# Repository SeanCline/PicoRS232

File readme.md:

# PicoRS232

>⚠ I haven't had this PCB design manufactured yet so there may be bugs. Here be dragons.

This PCB connects 6 RS232 UART ports to a Raspberry Pi Pico.
 1) Two ports are connected to the RP2040's 2 hardware UARTs.
 2) Four more ports are connected to the RP2040's PIO drivers for software UART.

The TX/RX pins line up with those from the [Pico UART Bridge](https://github.com/harrywalsh/pico-hw_and_pio-uart-gridge/tree/HW_and_pio_uarts) firmware so that firmware should work out-of-the-box.

Note: Flow control is not supported in this design. Only TX/RX are connected to each port. This was done to keep the BOM low and software simple.

## Schematic

## Board

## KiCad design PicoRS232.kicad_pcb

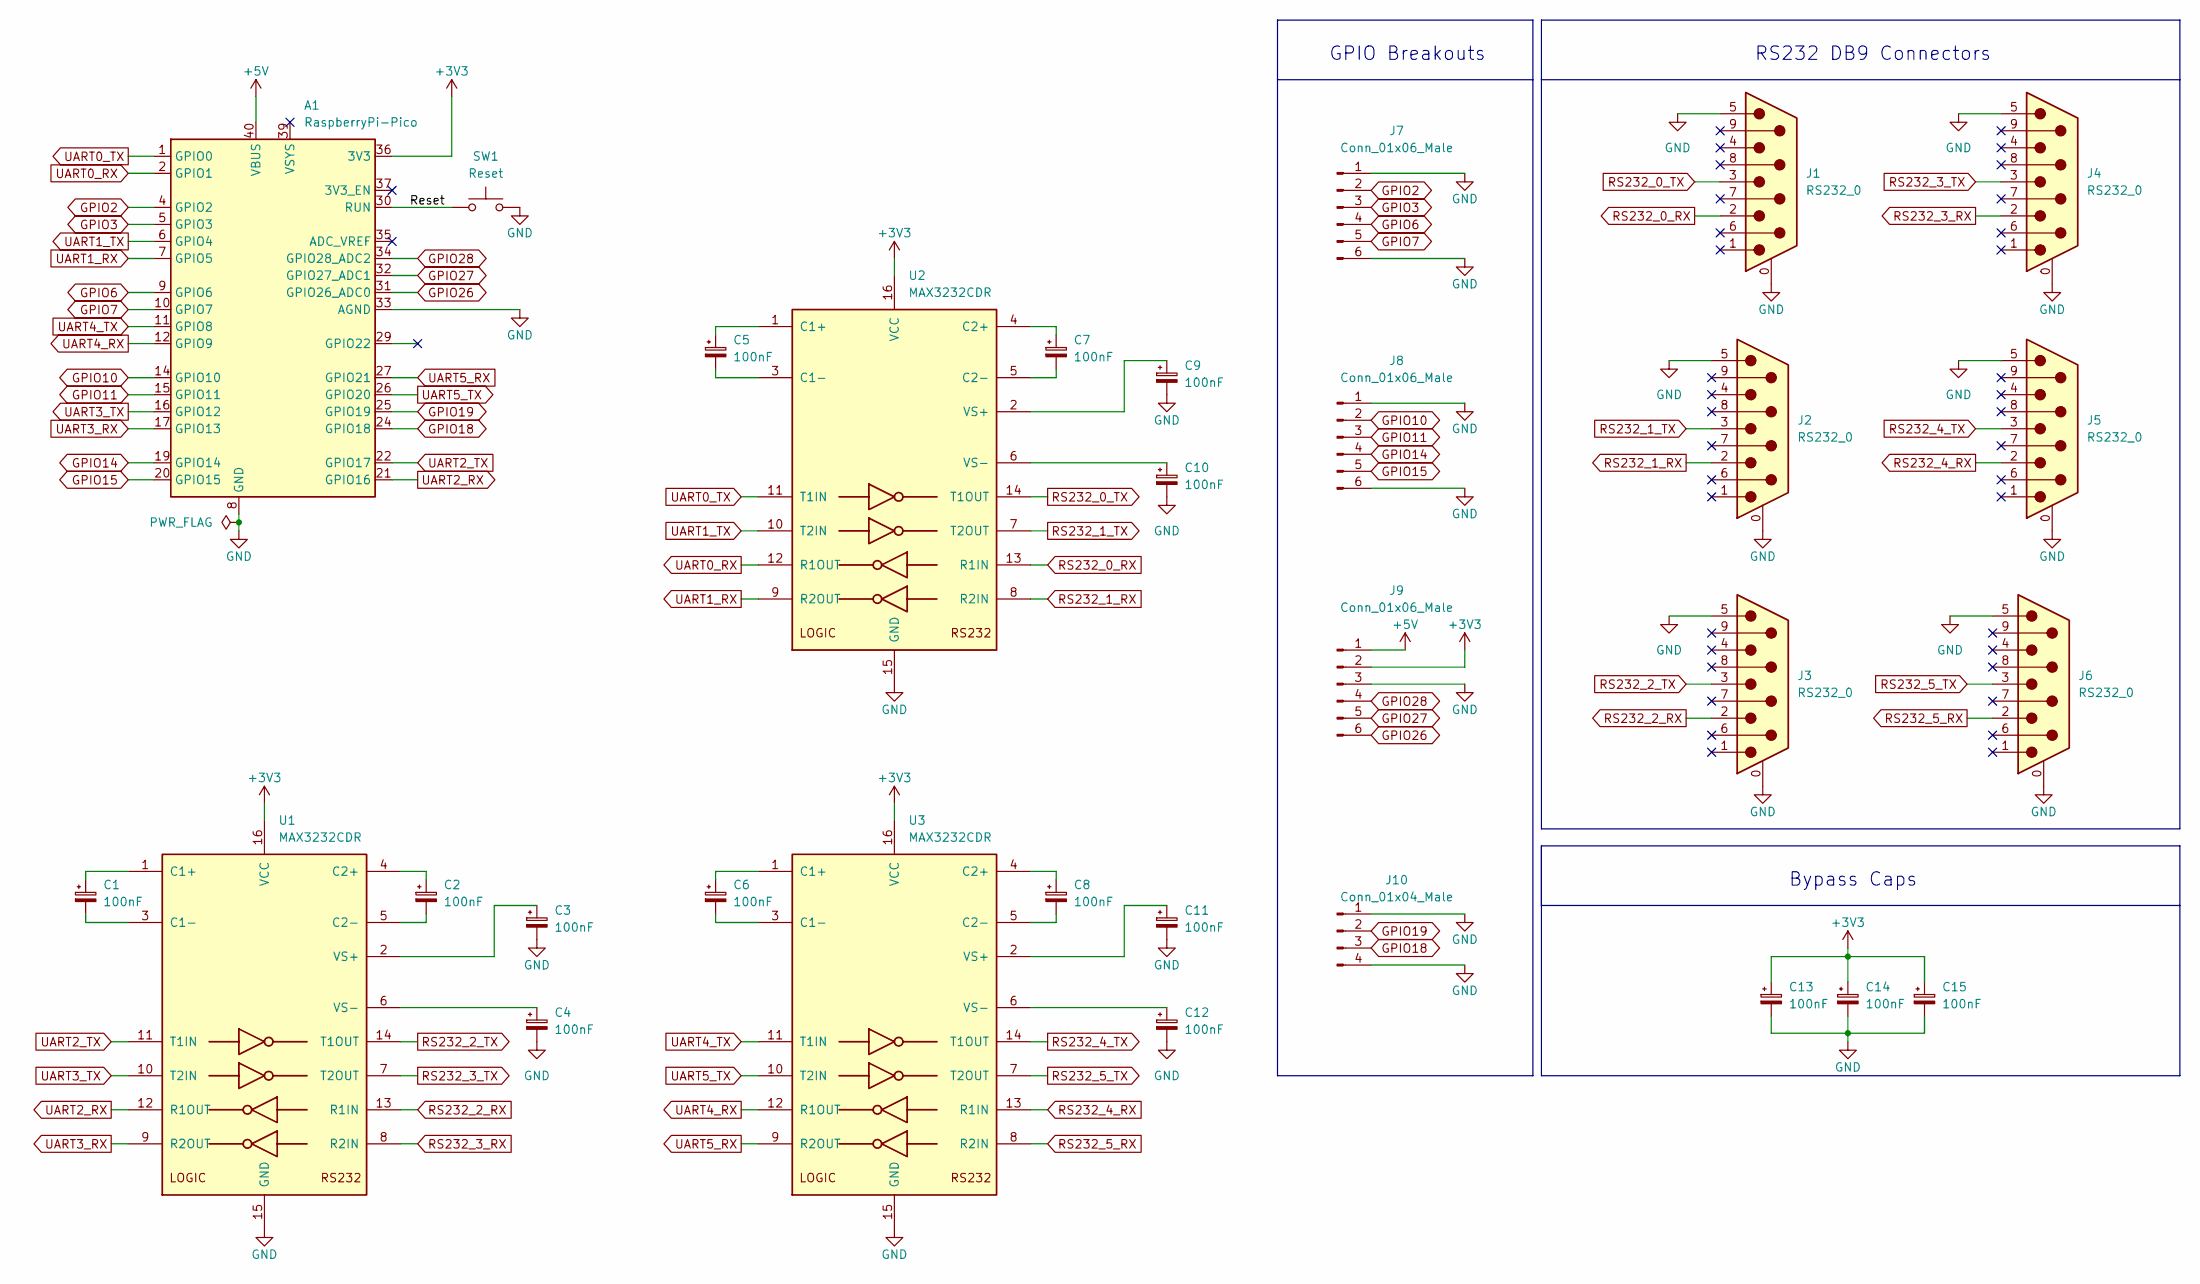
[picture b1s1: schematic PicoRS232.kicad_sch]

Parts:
A1: RaspberryPi-Pico; Raspberry_Pi_Pico_SMT_THT
C1, C2, C3, C4, C5, C6, C7, C8, C9, C10, C11, C12, C13, C14, C15: 100nF; C_0402_1005Metric; LCSC C307331
J1, J2, J3, J4, J5, J6: RS232_0; DSUB-9_Male_Horizontal_P2.77x2.84mm_EdgePinOffset7.70mm_Hou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; LCSC C141880
J7, J8, J9: Conn_01x06_Male; PinHeader_1x06_P2.54mm_Vertical; LCSC C225481
J10: Conn_01x04_Male; PinHeader_1x04_P2.54mm_Vertical; LCSC C225479
SW1: Reset; SW_SPST_SKQG_WithStem; LCSC C318889
U1, U2, U3: MAX3232CDR; SOIC-16_3.9x9.9mm_P1.27mm; LCSC C45843

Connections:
+3V3: A1.36 (3V3), C13.1, C14.1, C15.1, J9.2, U1.16 (VCC), U2.16 (VCC), U3.16 (VCC)
+5V: A1.40 (VBUS), J9.1
/Reset: A1.30 (RUN), SW1.1
GND: A1.3 (GND), A1.8 (GND), A1.13 (GND), A1.18 (GND), A1.23 (GND), A1.28 (GND), A1.33 (AGND), A1.38 (GND), C3.2, C4.2, C9.2, C10.2, C11.2, C12.2, C13.2, C14.2, C15.2, J1.0 (PAD), J1.5, J2.0 (PAD), J2.5, J3.0 (PAD), J3.5, J4.0 (PAD), J4.5, J5.0 (PAD), J5.5, J6.0 (PAD), J6.5, J7.1, J7.6, J8.1, J8.6, J9.3, J10.1, J10.4, SW1.2, U1.15 (GND), U2.15 (GND), U3.15 (GND)
GPIO2: A1.4 (GPIO2), J7.2
GPIO3: A1.5 (GPIO3), J7.3
GPIO6: A1.9 (GPIO6), J7.4
GPIO7: A1.10 (GPIO7), J7.5
GPIO10: A1.14 (GPIO10), J8.2
GPIO11: A1.15 (GPIO11), J8.3
GPIO14: A1.19 (GPIO14), J8.4
GPIO15: A1.20 (GPIO15), J8.5
GPIO18: A1.24 (GPIO18), J10.3
GPIO19: A1.25 (GPIO19), J10.2
GPIO26: A1.31 (GPIO26_ADC0), J9.6
GPIO27: A1.32 (GPIO27_ADC1), J9.5
GPIO28: A1.34 (GPIO28_ADC2), J9.4
unnamed: C1.1, U1.1 (C1+)
unnamed: C1.2, U1.3 (C1-)
unnamed: C2.1, U1.4 (C2+)
unnamed: C2.2, U1.5 (C2-)
unnamed: C3.1, U1.2 (VS+)
unnamed: C4.1, U1.6 (VS-)
unnamed: C5.1, U2.1 (C1+)
unnamed: C5.2, U2.3 (C1-)
unnamed: C6.1, U3.1 (C1+)
unnamed: C6.2, U3.3 (C1-)
unnamed: C7.1, U2.4 (C2+)
unnamed: C7.2, U2.5 (C2-)
unnamed: C8.1, U3.4 (C2+)
unnamed: C8.2, U3.5 (C2-)
unnamed: C9.1, U2.2 (VS+)
unnamed: C10.1, U2.6 (VS-)
unnamed: C11.1, U3.2 (VS+)
unnamed: C12.1, U3.6 (VS-)
RS232_0_RX: J1.2, U2.13 (R1IN)
RS232_0_TX: J1.3, U2.14 (T1OUT)
RS232_1_RX: J2.2, U2.8 (R2IN)
RS232_1_TX: J2.3, U2.7 (T2OUT)
RS232_2_RX: J3.2, U1.13 (R1IN)
RS232_2_TX: J3.3, U1.14 (T1OUT)
RS232_3_RX: J4.2, U1.8 (R2IN)
RS232_3_TX: J4.3, U1.7 (T2OUT)
RS232_4_RX: J5.2, U3.13 (R1IN)
RS232_4_TX: J5.3, U3.14 (T1OUT)
RS232_5_RX: J6.2, U3.8 (R2IN)
RS232_5_TX: J6.3, U3.7 (T2OUT)
UART0_RX: A1.2 (GPIO1), U2.12 (R1OUT)
UART0_TX: A1.1 (GPIO0), U2.11 (T1IN)
UART1_RX: A1.7 (GPIO5), U2.9 (R2OUT)
UART1_TX: A1.6 (GPIO4), U2.10 (T2IN)
UART2_RX: A1.21 (GPIO16), U1.12 (R1OUT)
UART2_TX: A1.22 (GPIO17), U1.11 (T1IN)
UART3_RX: A1.17 (GPIO13), U1.9 (R2OUT)
UART3_TX: A1.16 (GPIO12), U1.10 (T2IN)
UART4_RX: A1.12 (GPIO9), U3.12 (R1OUT)
UART4_TX: A1.11 (GPIO8), U3.11 (T1IN)
UART5_RX: A1.27 (GPIO21), U3.9 (R2OUT)
UART5_TX: A1.26 (GPIO20), U3.10 (T2IN)

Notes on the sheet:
Bypass Caps
GPIO Breakouts
RS232 DB9 Connectors

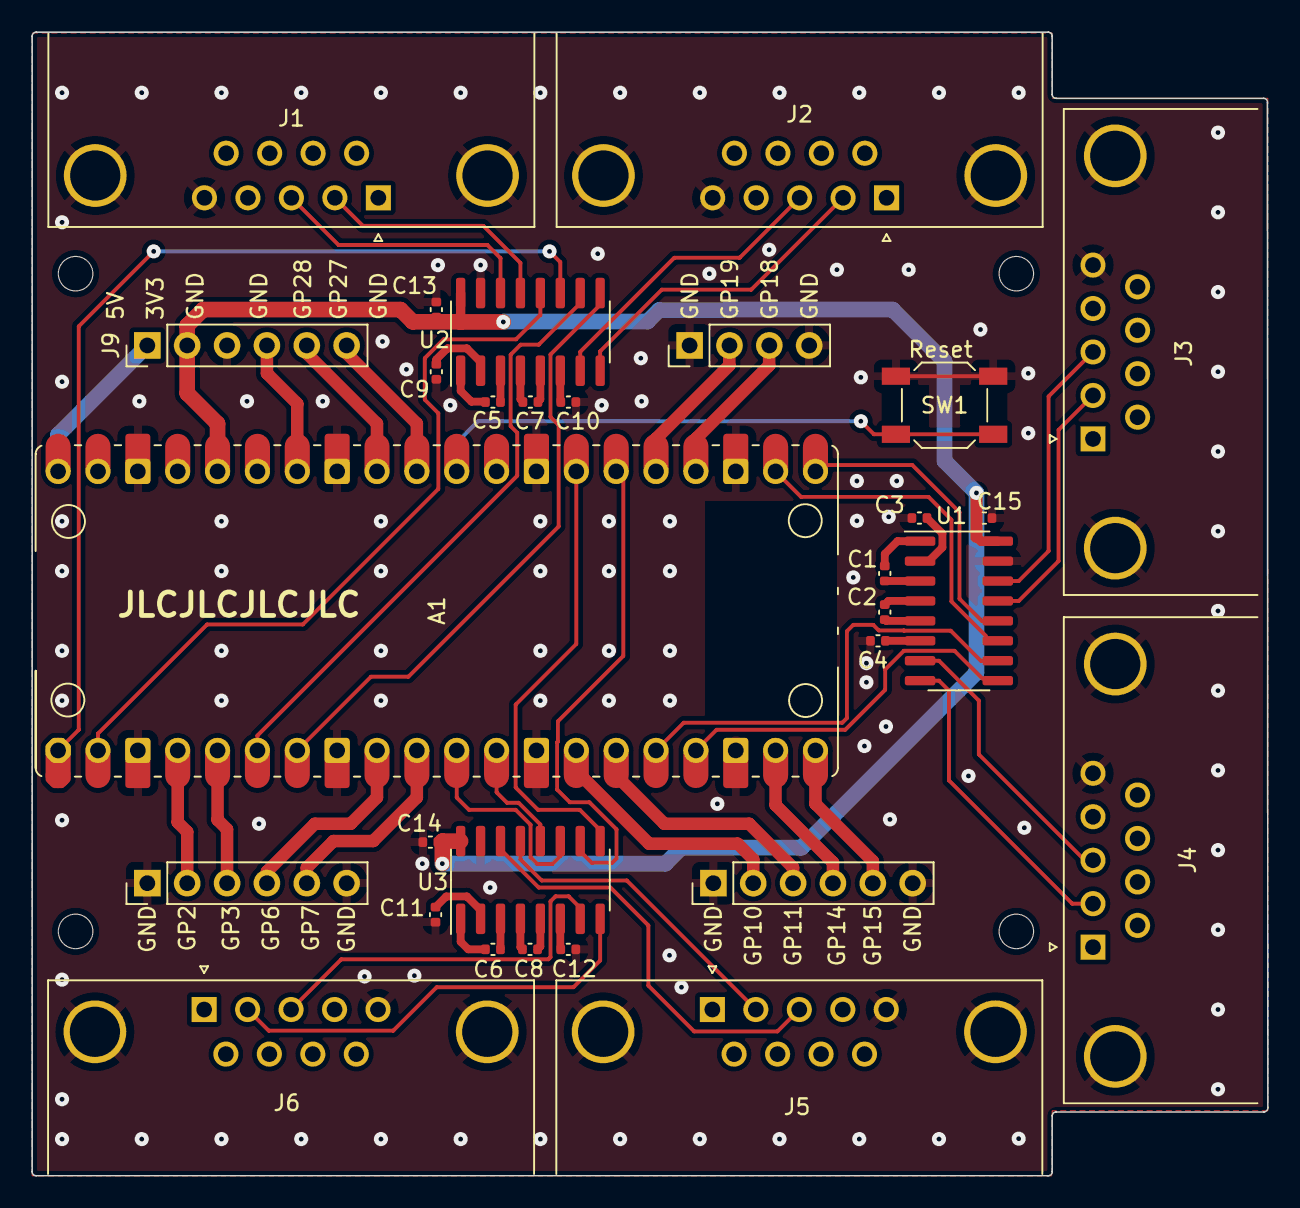
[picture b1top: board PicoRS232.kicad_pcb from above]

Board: 2 copper layers, 78.7 x 72.9 mm, 34 parts (0 on the bottom side), 59 nets.

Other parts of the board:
H1, H2, H3, H4: MountingHole_2.2mm_M2

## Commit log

2023-01-19 Initial Commit.
    Design is largely done, but needs lots of review before manufacture.
2023-01-19 Break out unused GPIO pins to headers.
2023-01-22 Organize schematic and add mounting holes.
2023-01-25 Silkscreen and cosmetic improvements to PCB.
2023-01-25 Add a simple readme with screenshots.
2023-01-25 Add a license.
2023-01-25 Update images to be more readable.
2023-01-26 Add a reset button and merge two pin headers.
2023-01-27 Change reset button to one JLCPCB has in stock.
2023-01-28 Add silkscreen with name, version, and url.
    Also, add pin header part numbers, but leave them out of the BOM.
